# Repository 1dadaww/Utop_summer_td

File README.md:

# Utop_summer_td

- [ESP32sheild](Esp32sheildwithADC/ESP32sheild.md)
- [Touch sensor RGB](Touch%20sensor%20RGB/RGB.md)
- [Power PCB and Mircroprocessors](Power%20PCB%20and%20Microprocessors/Power%20PCB%20and%20processors.md)
- [3D model robot](3D%20model%20Balancing%20Robot/3D%20model%20robot.md)
- [Touch sensor RGB instrunction for students](Touch%20sensor%20RGB/Instruction%20for%20students.md)
- [Questions from Edstem](Power%20PCB%20and%20Microprocessors/Questionsfromedstem.md)

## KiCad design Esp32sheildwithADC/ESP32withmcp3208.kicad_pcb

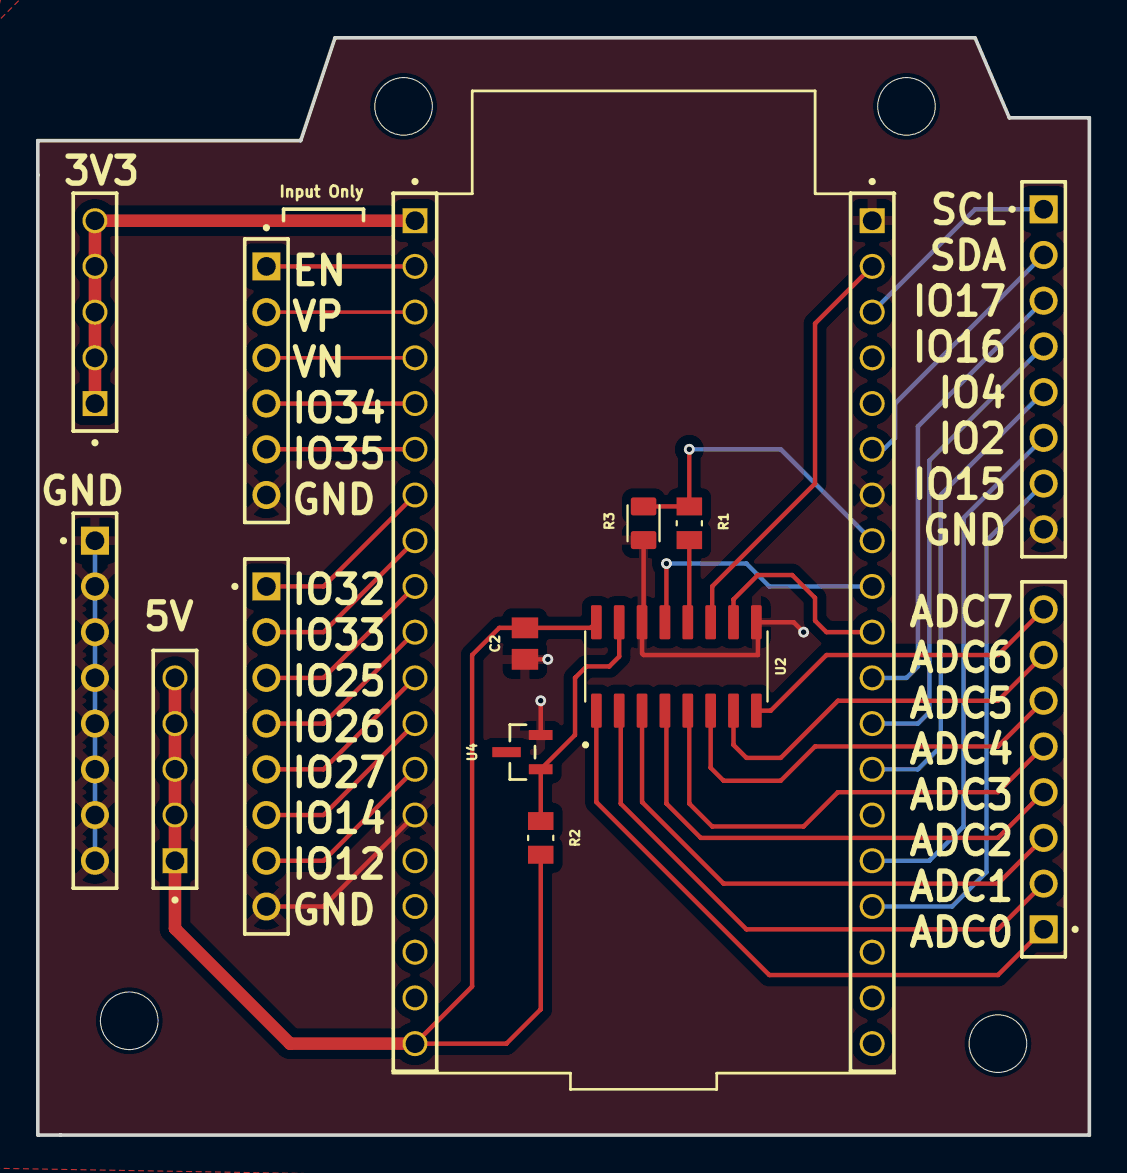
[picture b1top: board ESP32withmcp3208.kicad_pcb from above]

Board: 2 copper layers, 58.4 x 61.0 mm, 15 parts (0 on the bottom side), 36 nets.

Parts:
C2: C0805C104K5RACTU; CAPC2012X88N
J1, J4: SSW-119-01-G-S; SAMTEC_SSW-119-01-G-S
J2: SSW-106-01-X-S; SAMTEC_SSW-106-01-X-S
J3, J5, J8, J9: SSW-108-XX-X-S; SAMTEC_SSW-108-XX-X-S
J6, J7: SSW-105-01-G-S; SAMTEC_SSW-105-01-G-S
R1: CRGH0805J6K8; RESC2012X65N
R2: CRGH0805F1K0; RESC2012X65N
R3: CRG0805F10K; RESC2012X65N
U2: MCP3208-CI_SL; SOIC127P600X175-16N
U4: LM4040AIM3-4.1/NOPB; DBZ3

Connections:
/2: J4.15, J5.06
/3V3: J1.01, J6.01, J6.02, J6.03, J6.04, J6.05
/4: J4.13, J5.05
/4.096Vref: R2.2, U2.15 (VREF), U4.1 (CATHODE)
/5: J4.10, U2.10 (~CS/SHDN)
/5V: C2.1, J1.19, J7.01, J7.02, J7.03, J7.04, J7.05, R2.1, U2.16 (VDD)
/12: J1.13, J3.07
/14: J1.12, J3.06
/15: J4.16, J5.07
/16: J4.12, J5.04
/17: J4.11, J5.03
/18: J4.09, U2.13 (CLK)
/19: J4.08, R1.2, R3.1
/21: J4.06, J5.02
/22: J4.03, J5.01
/23: J4.02, U2.11 (DIN)
/25: J1.09, J3.03
/26: J1.10, J3.04
/27: J1.11, J3.05
/32: J1.07, J3.01
/33: J1.08, J3.02
/34: J1.05, J2.04
/35: J1.06, J2.05
/EN: J1.02, J2.01
/VN: J1.04, J2.03
/VP: J1.03, J2.02
GND: C2.2, J1.14, J2.06, J3.08, J4.01, J4.07, J5.08, J8.01, J8.02, J8.03, J8.04, J8.05, J8.06, J8.07, J8.08, R3.2, U2.9 (DGND), U2.14 (AGND), U4.2 (ANODE)
unnamed: J9.01, U2.1 (CH0)
unnamed: J9.02, U2.2 (CH1)
unnamed: J9.03, U2.3 (CH2)
unnamed: J9.04, U2.4 (CH3)
unnamed: J9.05, U2.5 (CH4)
unnamed: J9.06, U2.6 (CH5)
unnamed: J9.07, U2.7 (CH6)
unnamed: J9.08, U2.8 (CH7)
unnamed: R1.1, U2.12 (DOUT)

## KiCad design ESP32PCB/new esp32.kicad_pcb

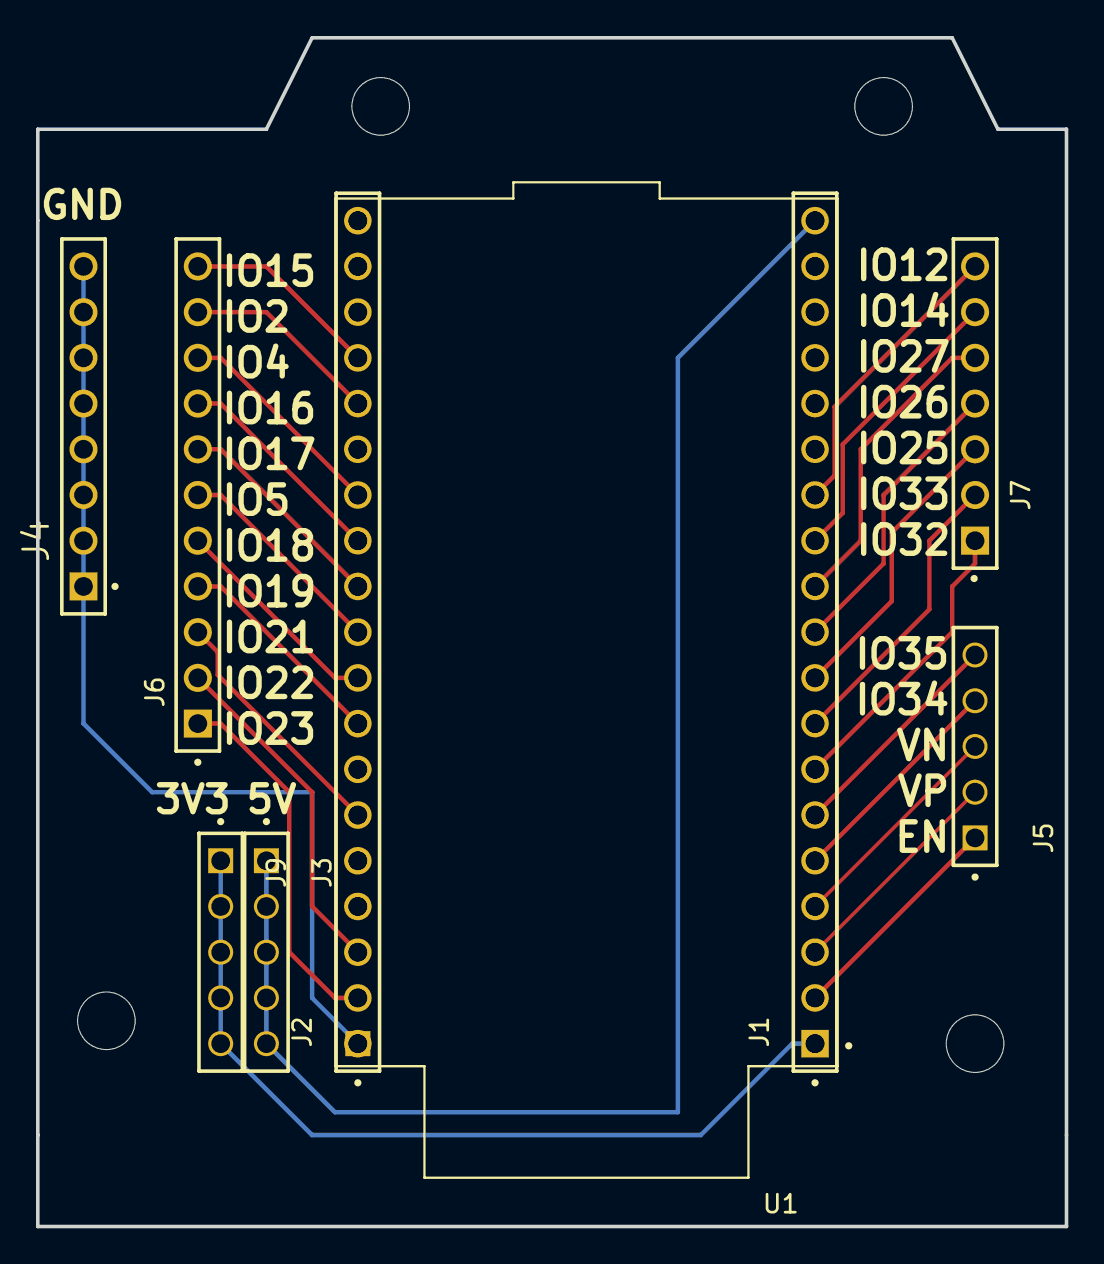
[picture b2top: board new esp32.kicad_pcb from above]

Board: 2 copper layers, 57.2 x 66.0 mm, 9 parts (0 on the bottom side), 38 nets.

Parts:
J1, J2: SSW-119-01-G-S; SAMTEC_SSW-119-01-G-S
J3, J5, J9: SSW-105-01-G-S; SAMTEC_SSW-105-01-G-S
J4: SSW-108-XX-X-S; SAMTEC_SSW-108-XX-X-S
J6: SSW-111-01-X-S; SAMTEC_SSW-111-01-X-S
J7: SSW-107-01-X-S; SAMTEC_SSW-107-01-X-S
U1: ESP32-DEVKITC; MODULE_ESP32-DEVKITC

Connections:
/0: J2.14, U1.25 (IO0)
/2: J2.15, J6.10, U1.24 (IO2)
/3V3: J1.01, J9.01, J9.02, J9.03, J9.04, J9.05, U1.1 (3V3)
/4: J2.13, J6.09, U1.26 (IO4)
/5: J2.10, J6.06, U1.29 (IO5)
/5V: J1.19, J3.01, J3.02, J3.03, J3.04, J3.05, U1.19 (EXT_5V)
/12: J1.13, J7.07, U1.13 (IO12)
/13: J1.15, U1.15 (IO13)
/14: J1.12, J7.06, U1.12 (IO14)
/15: J2.16, J6.11, U1.23 (IO15)
/16: J2.12, J6.08, U1.27 (IO16)
/17: J2.11, J6.07, U1.28 (IO17)
/18: J2.09, J6.05, U1.30 (IO18)
/19: J2.08, J6.04, U1.31 (IO19)
/21: J2.06, J6.03, U1.33 (IO21)
/22: J2.03, J6.02, U1.36 (IO22)
/23: J2.02, J6.01, U1.37 (IO23)
/25: J1.09, J7.03, U1.9 (IO25)
/26: J1.10, J7.04, U1.10 (IO26)
/27: J1.11, J7.05, U1.11 (IO27)
/32: J1.07, J7.01, U1.7 (IO32)
/33: J1.08, J7.02, U1.8 (IO33)
/34: J1.05, J5.04, U1.5 (IO34)
/35: J1.06, J5.05, U1.6 (IO35)
/CLK: J2.19, U1.20 (CLK)
/CMD: J1.18, U1.18 (CMD)
/D0: J2.18, U1.21 (SD0)
/D1: J2.17, U1.22 (SD1)
/D2: J1.16, U1.16 (SD2)
/D3: J1.17, U1.17 (SD3)
/EN: J1.02, J5.01, U1.2 (EN)
/GND1: J1.14, U1.14 (GND1)
/GND2: J2.07, U1.32 (GND2)
/GND3: J2.01, J4.01, J4.02, J4.03, J4.04, J4.05, J4.06, J4.07, J4.08, U1.38 (GND3)
/RX0: J2.05, U1.34 (RXD0)
/TX0: J2.04, U1.35 (TXD0)
/VN: J1.04, J5.03, U1.4 (SENSOR_VN)
/VP: J1.03, J5.02, U1.3 (SENSOR_VP)

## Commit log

2024-07-10 Create ESP32pcbdesign
2024-08-12 Create MCP3208testcode
2024-08-12 Create Tesing
2024-08-12 Testing code for mcp3208
    This is a basic code of the configutarion of MCP3208.
2024-08-12 PCB design
    This folder containing the schematic and PCB layout of the sheild design.
2024-08-12 Add files via upload
    ESP32 pinout
2024-08-12 Create a
2024-08-12 Add files via upload
    The adc_testrgb.py file reads the analog readings from the frequency-to-analog voltage output and changes the color based on the changes in the analog input.
    The RGB_all_combinations.py file detects if the four pads are touched and returns them as boolean constants. The main part checks all combinations of the four touch pads and produces an oscillating o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
2024-08-12 Add files via upload
    Laser cut file for RGB
2024-08-12 Add files via upload
    3D model of the connector to the acrylic on PCB
2024-08-12 Create 3Dprint Balancing robot
2024-08-12 Create balancing Robot
2024-08-12 Create 3D model Balancing Robot
2024-08-12 Rename Screenshot 2024-08-12 133317.png to ESP32pinout.png
2024-08-12 Rename image.png to ESP32PCB.png
2024-08-12 Add files via upload
    code to test mcp3208 and mpu6050
2024-08-12 Rename Screenshot 2024-08-12 155249.png to 3Dmodel
2024-08-12 Rename Screenshot 2024-08-12 155326.png to PCBRGB.png
2024-08-12 Rename Screenshot 2024-08-12 155249.png to Assemble design.png
2024-08-12 Rename Screenshot 2024-08-12 164859.png to Top.png
2024-08-12 Rename Screenshot 2024-08-12 165001.png to Bot.png
2024-08-12 Rename ESP32 sheild.md to ESP32sheild.md
2024-08-13 Rename Screenshot 2024-08-13 115426.png to powerpcb.png
2024-08-14 Rename Screenshot 2024-08-13 163919.png to circuit.png
2024-08-14 Rename USBcable.jpg to cable.jpg
2024-08-14 Rename Power PCB and Microprocessors Dev.md to Power PCB and processors.md
2024-08-20 Rename connector5mm v2.stl to connector5mm.stl
2024-08-21 Rename Instructionstu.md to Instruction for students.md
2024-08-22 Rename image.png to Assemble design.png
2024-08-22 Rename Screenshot 2024-08-22 160007.png to Assemble design.png
2024-08-22 Rename Screenshot 2024-08-22 160007.png to As.png
